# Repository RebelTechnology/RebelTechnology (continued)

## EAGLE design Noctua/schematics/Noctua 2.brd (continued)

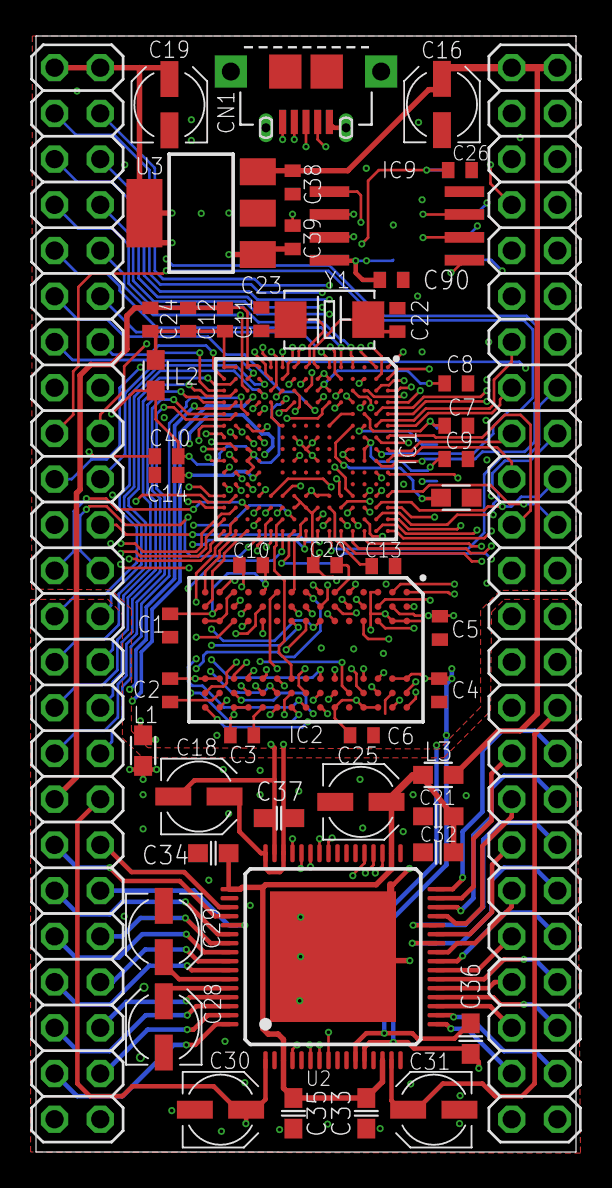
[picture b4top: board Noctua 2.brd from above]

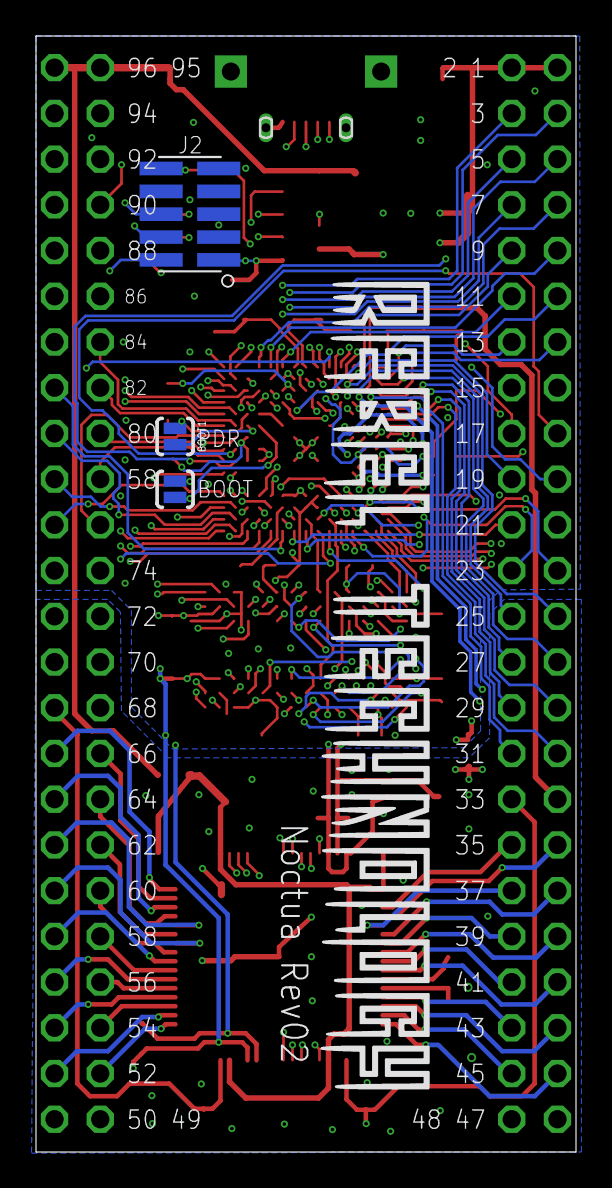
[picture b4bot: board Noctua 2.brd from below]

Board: 4 copper layers, 30.0 x 62.0 mm, 54 parts (3 on the bottom side), 171 nets.

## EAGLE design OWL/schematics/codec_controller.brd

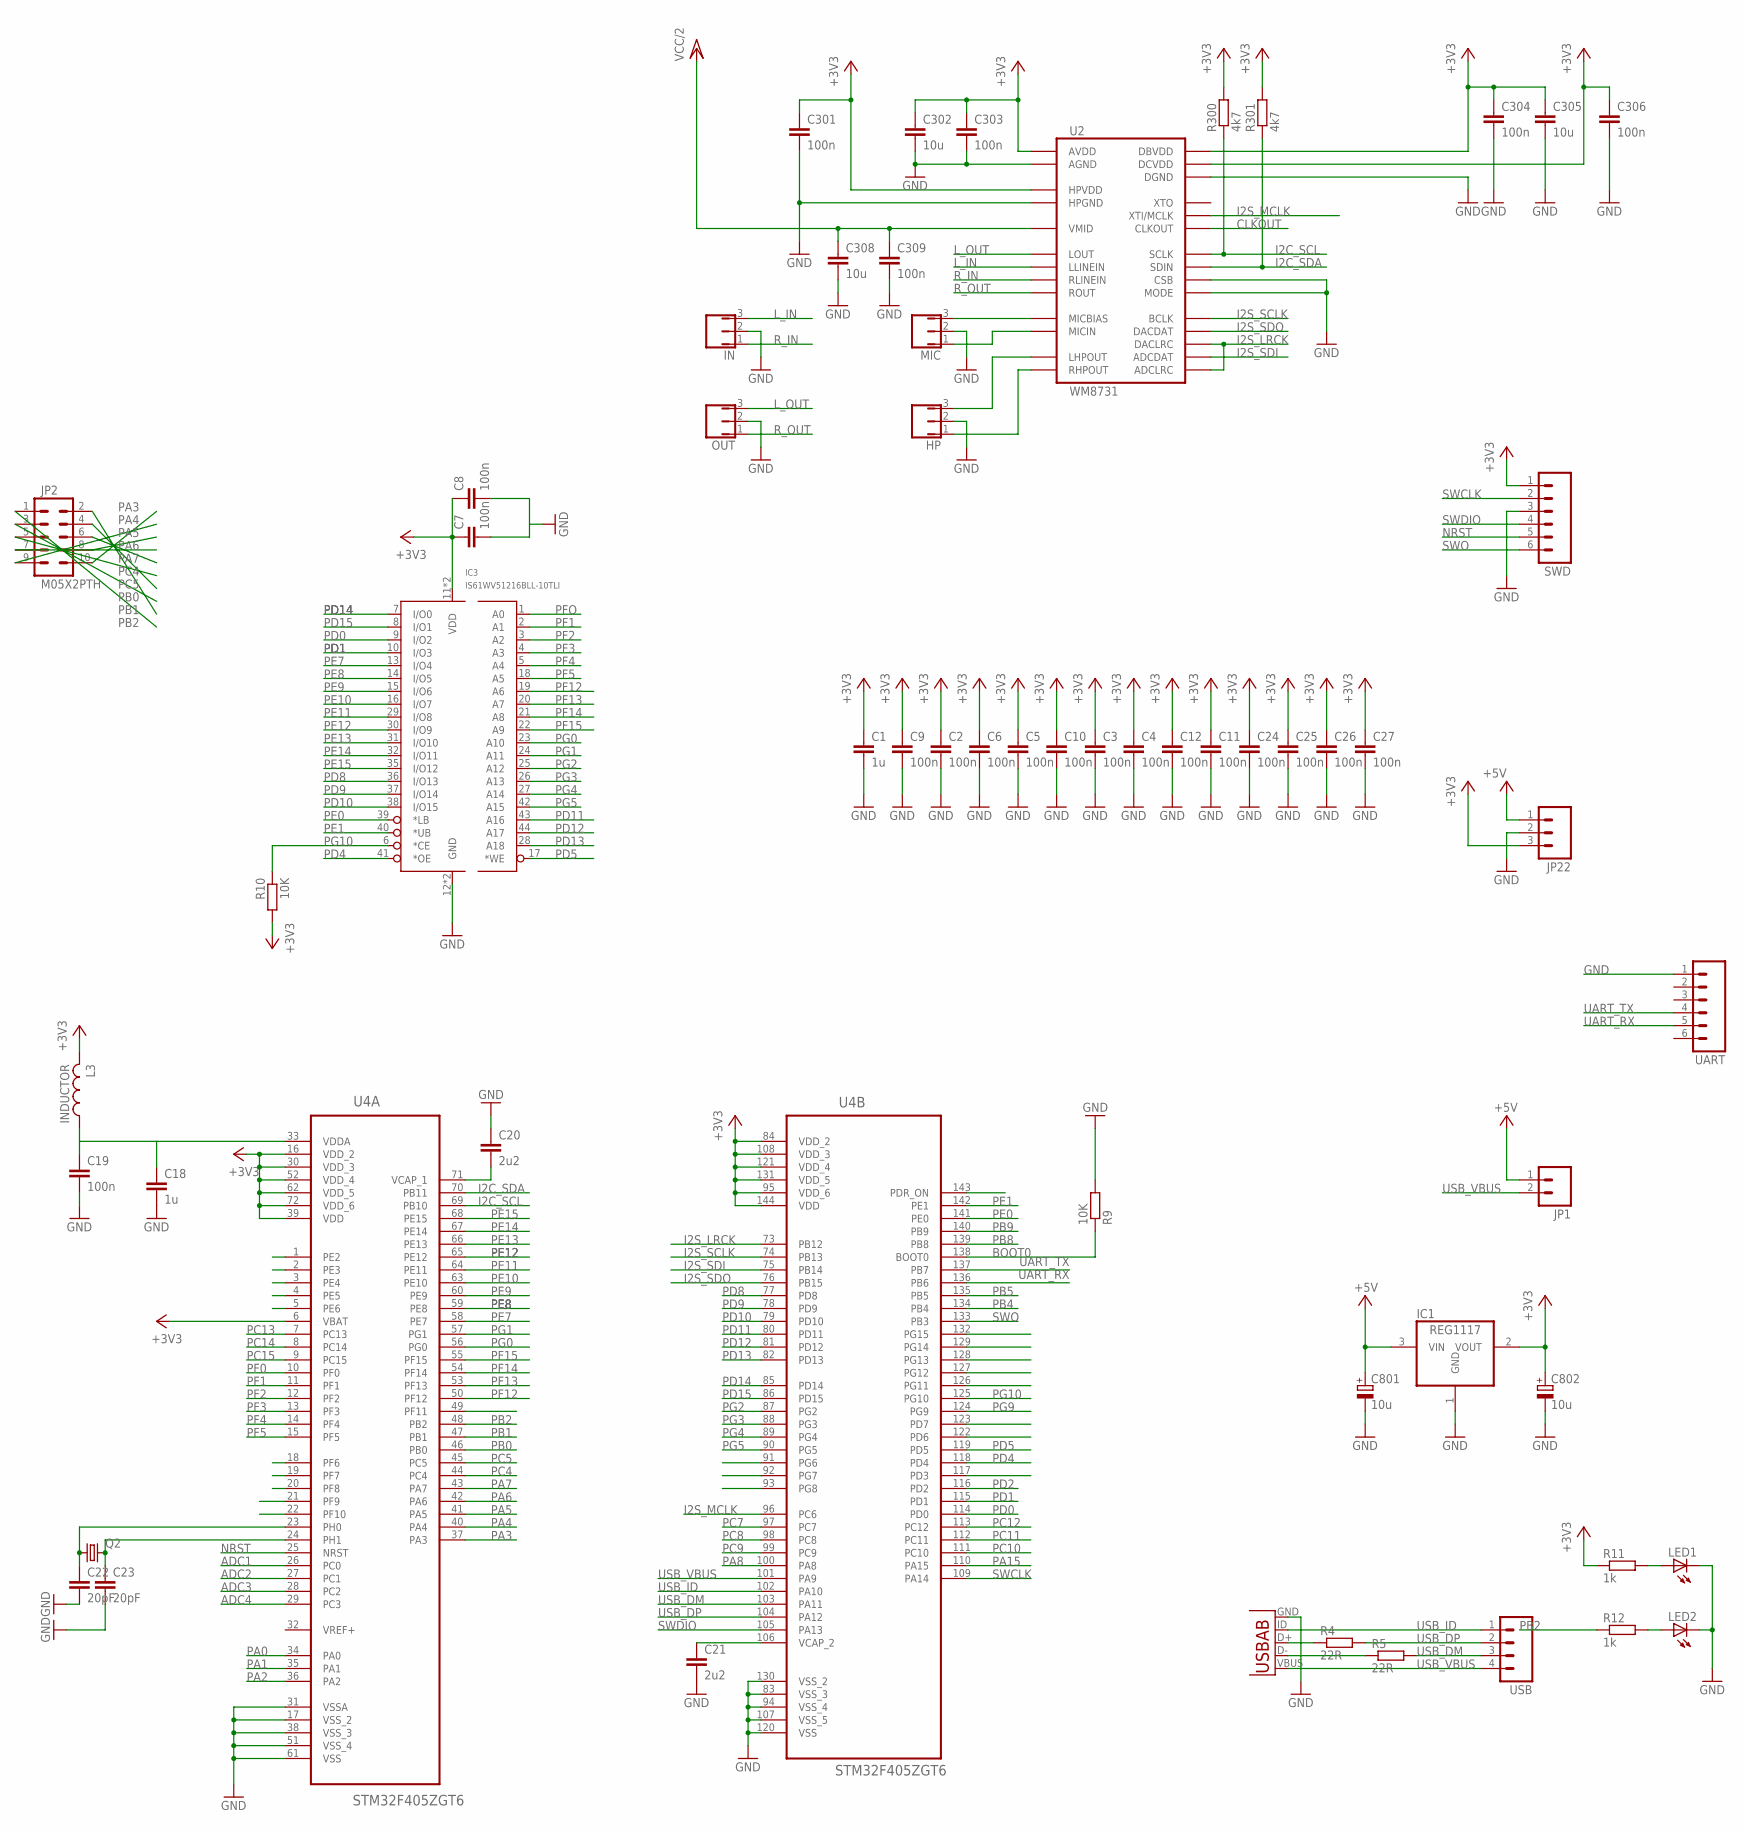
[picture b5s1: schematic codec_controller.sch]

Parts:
C1, C18: 1u; C0603
C2, C3, C4, C5, C6, C7, C8, C9, C10, C11, C12, C19, C24, C25, C26, C27, C301, C303, C304, C306, C309: 100n; C0603
C20, C21: 2u2; C0603
C22, C23: 20pF; C0603
C302, C305, C308: 10u; C1206
C801, C802: 10u; PANASONIC_A
HP: JMP/3P/SIP
IC1: REG1117; SOT223
IC3: IS61WV51216BLL-10TLI; TSOP44-II
IN: JMP/3P/SIP
JP1: M02PTH; 1X02
JP2: M05X2PTH; AVR_ICSP
JP22: M03PTH; 1X03
L3: INDUCTOR; 0603
LED1, LED2: LED1206; LED-1206
MIC: JMP/3P/SIP
OUT: JMP/3P/SIP
Q2: CRYSTALHC49UP; HC49UP
R4, R5: 22R; R0603
R9, R10: 10K; R0603
R11, R12: 1k; R0603
R300, R301: 4k7; R0603
SWD: M06SIP; 1X06
U2: WM8731; 28-SSOP
U3: USB-AB; USB-AB-MICRO-SMD
U4: STM32F405ZGT6; QFP50P2200X2200X160-144N
UART: M06SIP; 1X06
USB: M04PTH; 1X04

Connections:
+3V3: C1.1, C2.1, C3.1, C4.1, C5.1, C6.1, C7.1, C8.1, C9.1, C10.1, C11.1, C12.1, C24.1, C25.1, C26.1, C27.1, C301.1, C302.1, C303.1, C304.1, C305.1, C306.1, C802.+, IC1.2 (VOUT), IC3.11 (VDD), IC3.33 (VDD), JP22.3, L3.2, R10.2, R11.1, R300.2, R301.2, SWD.1, U2.P$1 (DBVDD), U2.P$8 (HPVDD), U2.P$14 (AVDD), U2.P$27 (DCVDD), U4.6 (VBAT), U4.16 (VDD_2), U4.30 (VDD_3), U4.39 (VDD), U4.52 (VDD_4), U4.62 (VDD_5), U4.72 (VDD_6), U4.84 (VDD_2), U4.95 (VDD_6), U4.108 (VDD_3), U4.121 (VDD_4), U4.131 (VDD_5), U4.144 (VDD); also elsewhere on the board
+5V: C801.+, IC1.3 (VIN), JP1.1, JP22.1; also elsewhere on the board
ADC1: U4.26 (PC0); also elsewhere on the board
ADC2: U4.27 (PC1); also elsewhere on the board
ADC3: U4.28 (PC2); also elsewhere on the board
ADC4: U4.29 (PC3); also elsewhere on the board
BOOT0: R9.1, U4.138 (BOOT0)
CLKOUT: U2.P$2 (CLKOUT)
GND: C1.2, C2.2, C3.2, C4.2, C5.2, C6.2, C7.2, C8.2, C9.2, C10.2, C11.2, C12.2, C18.2, C19.2, C20.1, C21.2, C22.2, C23.2, C24.2, C25.2, C26.2, C27.2, C301.2, C302.2, C303.2, C304.2, C305.2, C306.2, C308.2, C309.2, C801.-, C802.-, HP.2, IC1.1 (GND), IC3.12 (GND), IC3.34 (GND), IN.2, JP22.2, LED1.C, LED2.C, MIC.2, OUT.2, R9.2, SWD.3, U2.P$11 (HPGND), U2.P$15 (AGND), U2.P$21 (MODE), U2.P$22 (CSB), U2.P$28 (DGND), U3.GND, U4.17 (VSS_2), U4.31 (VSSA), U4.38 (VSS_3), U4.51 (VSS_4), U4.61 (VSS), U4.83 (VSS_3), U4.94 (VSS_4), U4.107 (VSS_5), U4.120 (VSS), U4.130 (VSS_2), UART.1; also elsewhere on the board
I2C_SCL: R300.1, U2.P$24 (SCLK), U4.69 (PB10)
I2C_SDA: R301.1, U2.P$23 (SDIN), U4.70 (PB11)
I2S_LRCK: U2.P$5 (DACLRC), U2.P$7 (ADCLRC), U4.73 (PB12)
I2S_MCLK: U2.P$25 (XTI/MCLK), U4.96 (PC6)
I2S_SCLK: U2.P$3 (BCLK), U4.74 (PB13)
I2S_SDI: U2.P$6 (ADCDAT), U4.75 (PB14)
I2S_SDO: U2.P$4 (DACDAT), U4.76 (PB15)
L_IN: IN.3, U2.P$20 (LLINEIN)
L_OUT: OUT.3, U2.P$12 (LOUT)
unnamed: MIC.3, U2.P$17 (MICBIAS)
unnamed: HP.3, U2.P$9 (LHPOUT)
unnamed: LED1.A, R11.2
unnamed: LED2.A, R12.2
unnamed: R4.1, U3.D+
unnamed: R5.1, U3.D-
unnamed: C23.1, Q2.2, U4.24 (PH1)
unnamed: C22.1, Q2.1, U4.23 (PH0)
unnamed: MIC.1, U2.P$18 (MICIN)
unnamed: HP.1, U2.P$10 (RHPOUT)
NRST: SWD.5, U4.25 (NRST)
PA0: U4.34 (PA0)
PA1: U4.35 (PA1)
PA2: U4.36 (PA2)
PA3: JP2.10, U4.37 (PA3)
PA4: JP2.9, U4.40 (PA4)
PA5: JP2.8, U4.41 (PA5)
PA6: JP2.7, U4.42 (PA6)
PA7: JP2.6, U4.43 (PA7)
PA8: U4.100 (PA8)
PA15: U4.110 (PA15)
PB0: JP2.3, U4.46 (PB0)
PB1: JP2.2, U4.47 (PB1)
PB2: JP2.1, R12.1, U4.48 (PB2)
PB4: U4.134 (PB4)
PB5: U4.135 (PB5)
PB8: U4.139 (PB8)
PB9: U4.140 (PB9)
PC4: JP2.5, U4.44 (PC4)
PC5: JP2.4, U4.45 (PC5)
PC7: U4.97 (PC7)
PC8: U4.98 (PC8)
PC9: U4.99 (PC9)
PC10: U4.111 (PC10)
PC11: U4.112 (PC11)
PC12: U4.113 (PC12)
PC13: U4.7 (PC13)
PC14: U4.8 (PC14)
PC15: U4.9 (PC15)
PD0: IC3.9 (I/O2), U4.114 (PD0)
PD1: IC3.10 (I/O3), U4.115 (PD1)
PD2: U4.116 (PD2)
PD3: U4.117 (PD3)
PD4: IC3.41 (*OE), U4.118 (PD4)
PD5: IC3.17 (*WE), U4.119 (PD5)
PD6: U4.122 (PD6)
PD7: U4.123 (PD7)
PD8: IC3.36 (I/O13), U4.77 (PD8)
PD9: IC3.37 (I/O14), U4.78 (PD9)
PD10: IC3.38 (I/O15), U4.79 (PD10)
PD11: IC3.43 (A16), U4.80 (PD11)
PD12: IC3.44 (A17), U4.81 (PD12)
PD13: IC3.28 (A18), U4.82 (PD13)
PD14: IC3.7 (I/O0), U4.85 (PD14)
PD15: IC3.8 (I/O1), U4.86 (PD15)
PE0: IC3.39 (*LB), U4.141 (PE0)
PE1: IC3.40 (*UB), U4.142 (PE1)
PE7: IC3.13 (I/O4), U4.58 (PE7)
PE8: IC3.14 (I/O5), U4.59 (PE8)
PE9: IC3.15 (I/O6), U4.60 (PE9)
PE10: IC3.16 (I/O7), U4.63 (PE10)
PE11: IC3.29 (I/O8), U4.64 (PE11)
PE12: IC3.30 (I/O9), U4.65 (PE12)
PE13: IC3.31 (I/O10), U4.66 (PE13)
PE14: IC3.32 (I/O11), U4.67 (PE14)
PE15: IC3.35 (I/O12), U4.68 (PE15)
PF0: U4.10 (PF0)
PF1: IC3.2 (A1), U4.11 (PF1)
PF2: IC3.3 (A2), U4.12 (PF2)
PF3: IC3.4 (A3), U4.13 (PF3)
PF4: IC3.5 (A4), U4.14 (PF4)
PF5: IC3.18 (A5), U4.15 (PF5)
PF9: U4.20 (PF8)
PF12: IC3.19 (A6), U4.50 (PF12)
PF13: IC3.20 (A7), U4.53 (PF13)
PF14: IC3.21 (A8), U4.54 (PF14)
PF15: IC3.22 (A9), U4.55 (PF15)
PFO: IC3.1 (A0)
PG0: IC3.23 (A10), U4.56 (PG0)
PG1: IC3.24 (A11), U4.57 (PG1)
PG2: IC3.25 (A12), U4.87 (PG2)
PG3: IC3.26 (A13), U4.88 (PG3)
PG4: IC3.27 (A14), U4.89 (PG4)
PG5: IC3.42 (A15), U4.90 (PG5)
PG9: U4.124 (PG9)
PG10: IC3.6 (*CE), R10.1, U4.125 (PG10)
R_IN: IN.1, U2.P$19 (RLINEIN)
R_OUT: OUT.1, U2.P$13 (ROUT)
SWCLK: SWD.2, U4.109 (PA14)
SWDIO: SWD.4, U4.105 (PA13)
SWO: SWD.6, U4.133 (PB3)
UART_RX: U4.136 (PB6), UART.5
UART_TX: U4.137 (PB7), UART.4
USB_DM: R5.2, U4.103 (PA11), USB.3
USB_DP: R4.2, U4.104 (PA12), USB.2
USB_ID: U3.ID (USBID), U4.102 (PA10), USB.1
USB_VBUS: JP1.2, U3.VBUS, U4.101 (PA9), USB.4
VCAP1: C20.2, U4.71 (VCAP_1)
VCAP2: C21.1, U4.106 (VCAP_2)
VCC/2: C308.1, C309.1, U2.P$16 (VMID)
VDDA: C18.1, C19.1, L3.1, U4.32 (VREF+), U4.33 (VDDA)

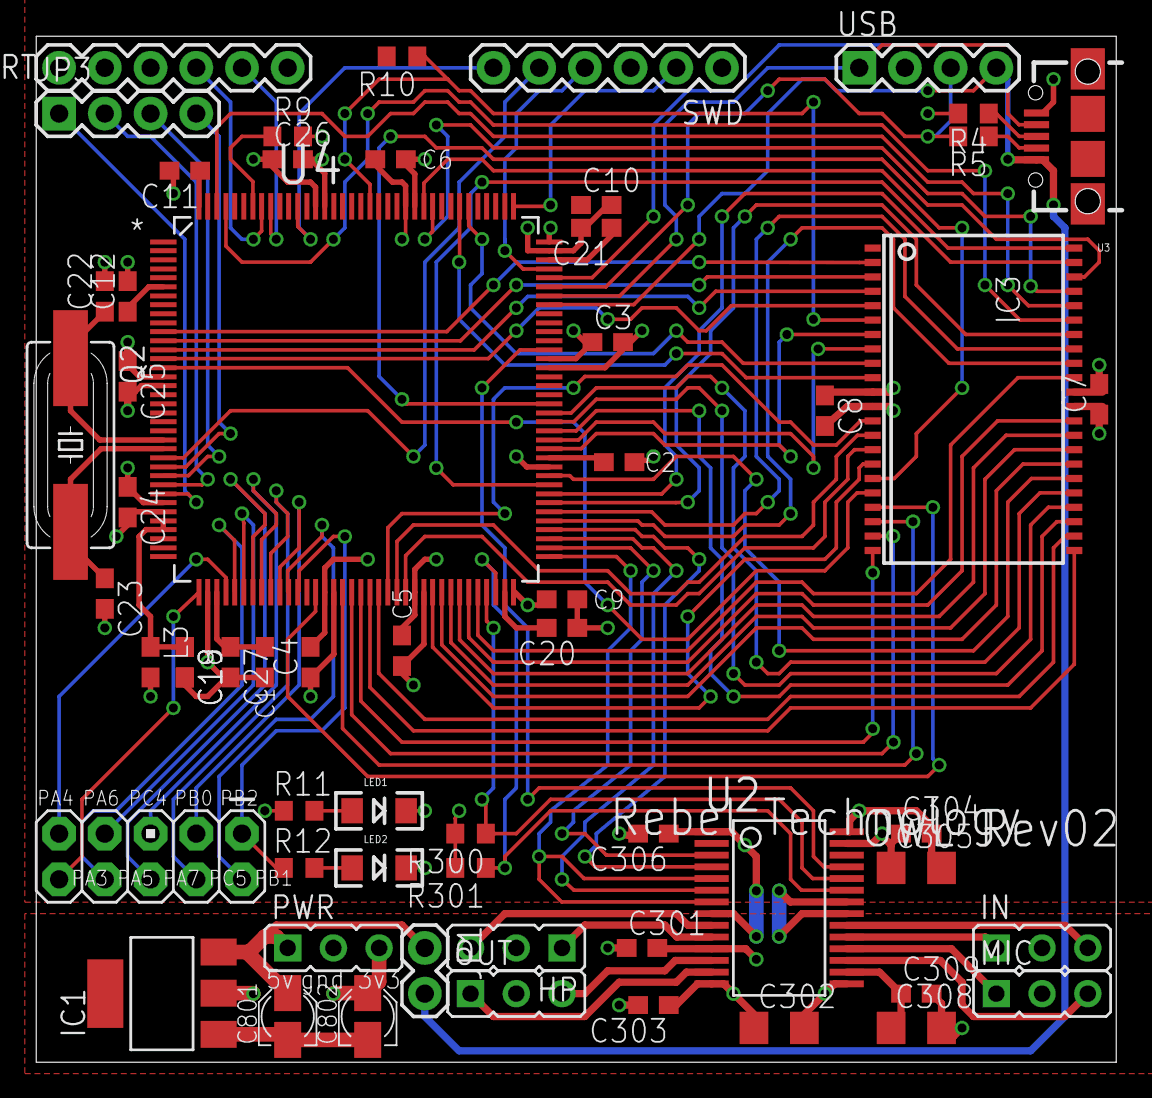
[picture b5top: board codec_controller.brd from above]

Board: 2 copper layers, 60.0 x 57.0 mm, 60 parts (0 on the bottom side), 92 nets.

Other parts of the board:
JP3: 1X04
PWR: JMP/3P/SIP

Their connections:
+3V3: PWR.3; also elsewhere on the board
+5V: PWR.1; also elsewhere on the board
ADC1: JP3.4; also elsewhere on the board
ADC2: JP3.3; also elsewhere on the board
ADC3: JP3.2; also elsewhere on the board
ADC4: JP3.1; also elsewhere on the board
GND: PWR.2; also elsewhere on the board

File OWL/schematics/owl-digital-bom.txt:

Partlist

Exported from owl-digital.sch at 14/08/2013 19:11

EAGLE Version 6.4.0 Copyright (c) 1988-2013 CadSoft

Assembly variant: 

Part     Value                Device                         Package                  Library       Sheet

ADC                           M04PTH                         1X04                     SparkFun      1
C1       1u                   C-EUC0603                      C0603                    resistor      1
C2       100n                 C-EUC0603                      C0603                    resistor      1
C3       100n                 C-EUC0603                      C0603                    resistor      1
C4       100n                 C-EUC0603                      C0603                    resistor      1
C5       100n                 C-EUC0603                      C0603                    resistor      1
C6       100n                 C-EUC0603                      C0603                    resistor      1
C7       100n                 C-EUC0603                      C0603                    resistor      1
C8       100n                 C-EUC0603                      C0603                    resistor      1
C9       100n                 C-EUC0603                      C0603                    resistor      1
C10      100n                 C-EUC0603                      C0603                    resistor      1
C11      100n                 C-EUC0603                      C0603                    resistor      1
C18      1u                   C-EUC0603                      C0603                    resistor      1
C19      100n                 C-EUC0603                      C0603                    resistor      1
C20      2u2                  C-EUC0603                      C0603                    resistor      1
C21      2u2                  C-EUC0603                      C0603                    resistor      1
C22      20pF                 C-EUC0603                      C0603                    resistor      1
C23      20pF                 C-EUC0603                      C0603                    resistor      1
C24      100n                 C-EUC0603                      C0603                    resistor      1
C25      100n                 C-EUC0603                      C0603                    resistor      1
C26      100n                 C-EUC0603                      C0603                    resistor      1
C27      100n                 C-EUC0603                      C0603                    resistor      1
C301     100n                 C-EUC0603                      C0603                    resistor      1
C302     10u                  C-EUC1206                      C1206                    resistor      1
C303     100n                 C-EUC0603                      C0603                    resistor      1
C304     100n                 C-EUC0603                      C0603                    resistor      1
C305     10u                  C-EUC1206                      C1206                    resistor      1
C306     100n                 C-EUC0603                      C0603                    resistor      1
C308     10u                  C-EUC1206                      C1206                    resistor      1
C309     100n                 C-EUC0603                      C0603                    resistor      1
C801     10u                  CPOL-EUA                       PANASONIC_A              resistor      1
C802     10u                  CPOL-EUA                       PANASONIC_A              resistor      1
HP                            JMP/3P/SIP                     JMP/3P/SIP               audioint      1
IC1      REG1117              REG1117                        SOT223                   burr-brown    1
IC3      IS61WV51216BLL-10TLI IS61WV51216BLL-10TLI           TSOP44-II                Rebel         1
IN                            JMP/3P/SIP                     JMP/3P/SIP               audioint      1
JP1                           M02PTH                         1X02                     SparkFun      1
JP2      M05X2PTH             M05X2PTH                       AVR_ICSP                 SparkFun      1
L3       INDUCTOR             INDUCTOR                       0603                     Rebel         1
LED1                          LED1206                        LED-1206                 SparkFun      1
LED2                          LED1206                        LED-1206                 SparkFun      1
MIC                           JMP/3P/SIP                     JMP/3P/SIP               audioint      1
OUT                           JMP/3P/SIP                     JMP/3P/SIP               audioint      1
PWR                           JMP/3P/SIP                     JMP/3P/SIP               audioint      1
Q2                            CRYSTALHC49UP                  HC49UP                   crystal       1
R4       22R                  R-EU_R0603                     R0603                    resistor      1
R5       22R                  R-EU_R0603                     R0603                    resistor      1
R9       10K                  R-EU_R0603                     R0603                    resistor      1
R10      10K                  R-EU_R0603                     R0603                    resistor      1
R11      1k                   R-EU_R0603                     R0603                    resistor      1
R12      1k                   R-EU_R0603                     R0603                    resistor      1
R300     4k7                  R-EU_R0603                     R0603                    resistor      1
R301     4k7                  R-EU_R0603                     R0603                    resistor      1
SWD                           M06SIP                         1X06                     SparkFun      1
U2       WM8731               WM8731                         28-SSOP                  audioint      1
U4       STM32F405ZGT6        STM32F405ZGT6                  QFP50P2200X2200X160-144N Rebel         1
UART                          M06SIP                         1X06                     SparkFun      1
USB                           M05PTH                         1X05                     SparkFun      1
USB1                          USB_HRS_ZX62-B-5PA(11)MICRO.B- HRS_ZX62D-AB-5P8_USB     USB_connector 1
